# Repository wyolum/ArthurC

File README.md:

ArthurC
=======

rev 2 of i2GPS - called ArthurC in honor of Arthur C Clarke, who coined the idea of GPS

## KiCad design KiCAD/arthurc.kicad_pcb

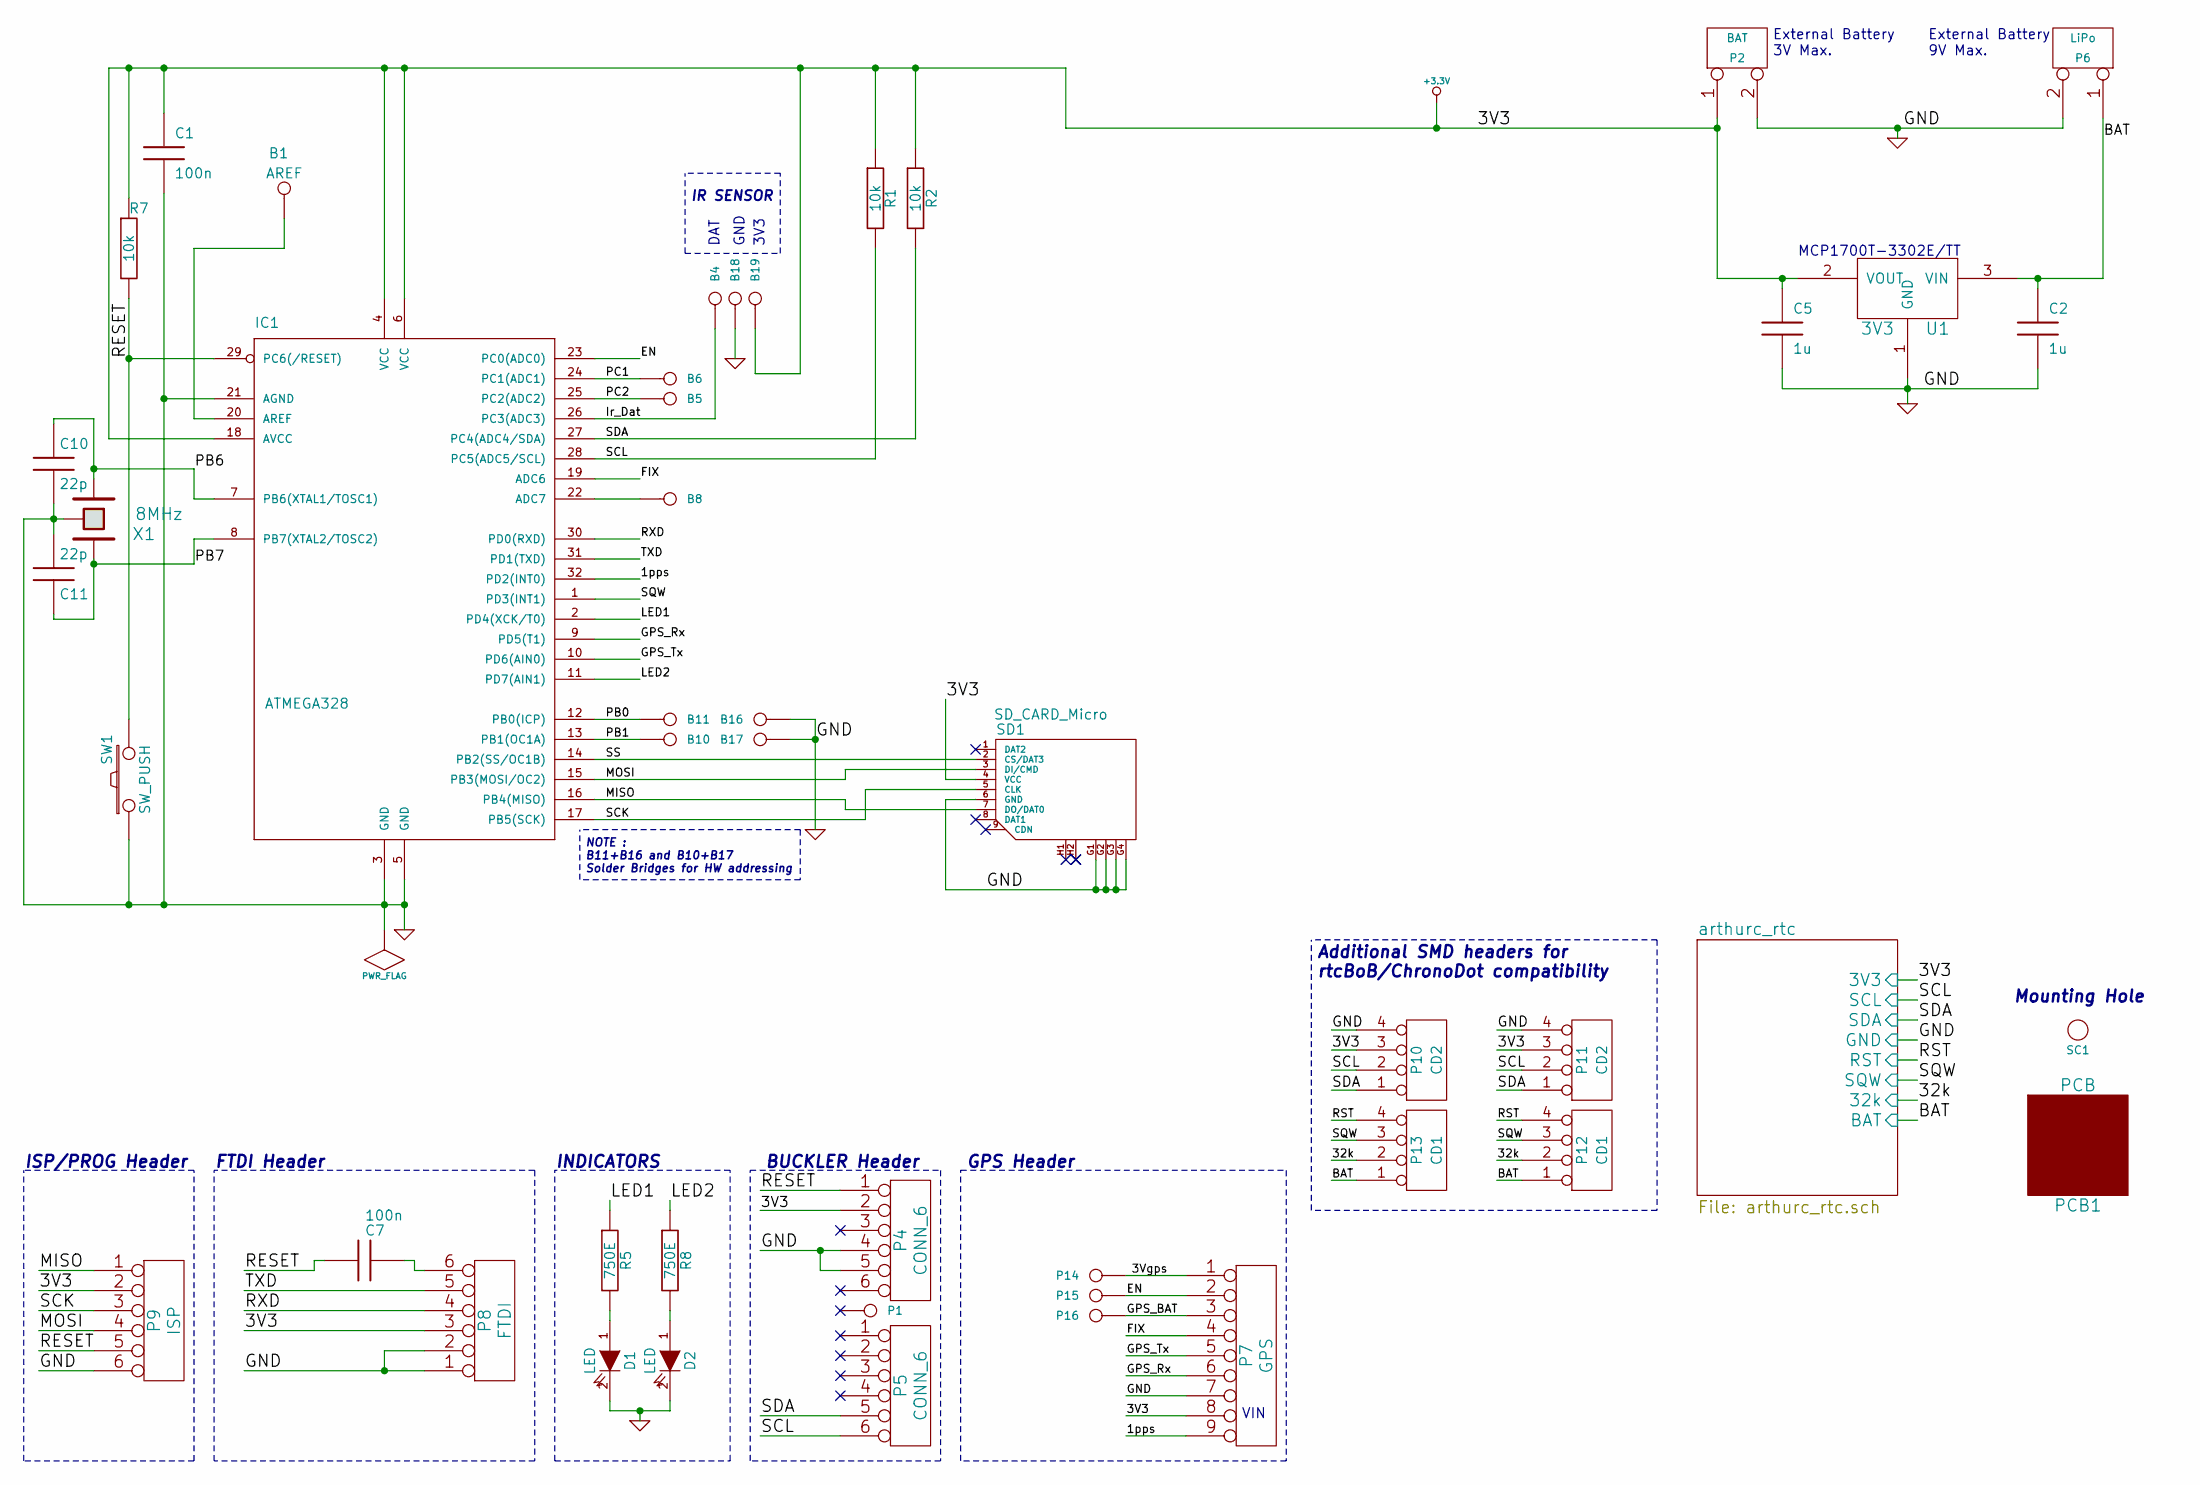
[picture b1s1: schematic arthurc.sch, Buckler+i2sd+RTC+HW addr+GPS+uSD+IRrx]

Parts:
B1: AREF
B4, B5, B6, B8, B18, B19: I/O; I%2fO
B10, B11, B16, B17: I/O; I%2fO_ADR
C1, C7: 100n; c_0805
C2, C5: 1u; c_0805
C10, C11: 22p; c_0805; Digikey 490-1734-1-ND
D1, D2: LED; d_0805
IC1: ATMEGA328; TQFP32
P1, P14, P15, P16: I/O; I%2fO
P2: BAT
P4, P5: CONN_6; PIN_ARRAY-6X1
P6: LiPo; pin_strip_2
P7: GPS; PIN_ARRAY-9X1
P8: FTDI; PIN_ARRAY-6X1
P9: ISP
P10, P11: CD2; Sck-04-F-SMT
P12, P13: CD1; Sck-04-F-SMT
PCB1: PCB
R1, R2, R7: 10k; r_0805
R5, R8: 750E; r_0805
SC1: SCREW; vite_3mm
SD1: SD_CARD_Micro
SW1: SW_PUSH; SW_SMD
U1: 3V3; SOT23-3; Part No MCP1700T-3302E/TT
X1: 8MHz; Xtal_SMD3

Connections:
+3.3V: B19.1, C1.1, C5.1, IC1.4 (VCC), IC1.6 (VCC), IC1.18 (AVCC), P2.1, P4.2, P7.8, P8.3, P9.2, P10.3, P11.3, R1.1, R2.1, R7.1, SD1.4 (VCC), U1.2 (VOUT); also elsewhere on the board
/1pps: IC1.32 (PD2(INT0)), P7.9
/3Vgps: P7.1, P14.1
/EN: IC1.23 (PC0(ADC0)), P7.2, P15.1
/FIX: IC1.19 (ADC6), P7.4
/GPS_BAT: P7.3, P16.1
/GPS_Rx: IC1.9 (PD5(T1)), P7.6
/GPS_Tx: IC1.10 (PD6(AIN0)), P7.5
/Ir_Dat: B4.1, IC1.26 (PC3(ADC3))
/LED1: IC1.2 (PD4(XCK/T0)), R5.1
/LED2: IC1.11 (PD7(AIN1)), R8.1
/MISO: IC1.16 (PB4(MISO)), P9.1, SD1.7 (DO/DAT0)
/MOSI: IC1.15 (PB3(MOSI/OC2)), P9.4, SD1.3 (DI/CMD)
/PB0: B11.1, IC1.12 (PB0(ICP))
/PB1: B10.1, IC1.13 (PB1(OC1A))
/PB6: C10.1, IC1.7 (PB6(XTAL1/TOSC1)), X1.1
/PB7: C11.2, IC1.8 (PB7(XTAL2/TOSC2)), X1.2
/PC1: B6.1, IC1.24 (PC1(ADC1))
/PC2: B5.1, IC1.25 (PC2(ADC2))
/RESET: C7.2, IC1.29 (PC6(/RESET)), P4.1, P9.5, R7.2, SW1.2
/RXD: IC1.30 (PD0(RXD)), P8.4
/SCK: IC1.17 (PB5(SCK)), P9.3, SD1.5 (CLK)
/SS: IC1.14 (PB2(SS/OC1B)), SD1.2 (CS/DAT3)
/TXD: IC1.31 (PD1(TXD)), P8.5
/arthurc_rtc/32k: P12.2, P13.2; also elsewhere on the board
/arthurc_rtc/BAT: C2.1, P6.1, P12.1, P13.1, U1.3 (VIN); also elsewhere on the board
/arthurc_rtc/RST: P12.4, P13.4; also elsewhere on the board
/arthurc_rtc/SCL: IC1.28 (PC5(ADC5/SCL)), P5.6, P10.2, P11.2, R1.2; also elsewhere on the board
/arthurc_rtc/SDA: IC1.27 (PC4(ADC4/SDA)), P5.5, P10.1, P11.1, R2.2; also elsewhere on the board
/arthurc_rtc/SQW: IC1.1 (PD3(INT1)), P12.3, P13.3; also elsewhere on the board
GND: B16.1, B17.1, B18.1, C1.2, C2.2, C5.2, C10.2, C11.1, D1.2 (K), D2.2 (K), IC1.3 (GND), IC1.5 (GND), IC1.21 (AGND), P2.2 (PM), P4.4, P4.5, P6.2 (PM), P7.7, P8.1, P8.2, P9.6, P10.4, P11.4, SD1.6 (GND), SD1.G1, SD1.G2, SD1.G3, SD1.G4, SW1.1, U1.1 (GND), X1.3; also elsewhere on the board
unnamed: B1.1, IC1.20 (AREF)
unnamed: B8.1, IC1.22 (ADC7)
unnamed: C7.1, P8.6
unnamed: D1.1 (A), R5.2
unnamed: D2.1 (A), R8.2

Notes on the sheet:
MCP1700T-3302E/TT
GPS Header
3V3
GND
DAT
IR SENSOR
NOTE : B11+B16 and B10+B17 Solder Bridges for HW addressing
External Battery 9V Max.
INDICATORS
FTDI Header
ISP/PROG Header
BUCKLER Header
Mounting Hole
Additional SMD headers for rtcBoB/ChronoDot compatibility
VIN
External Battery 3V Max.

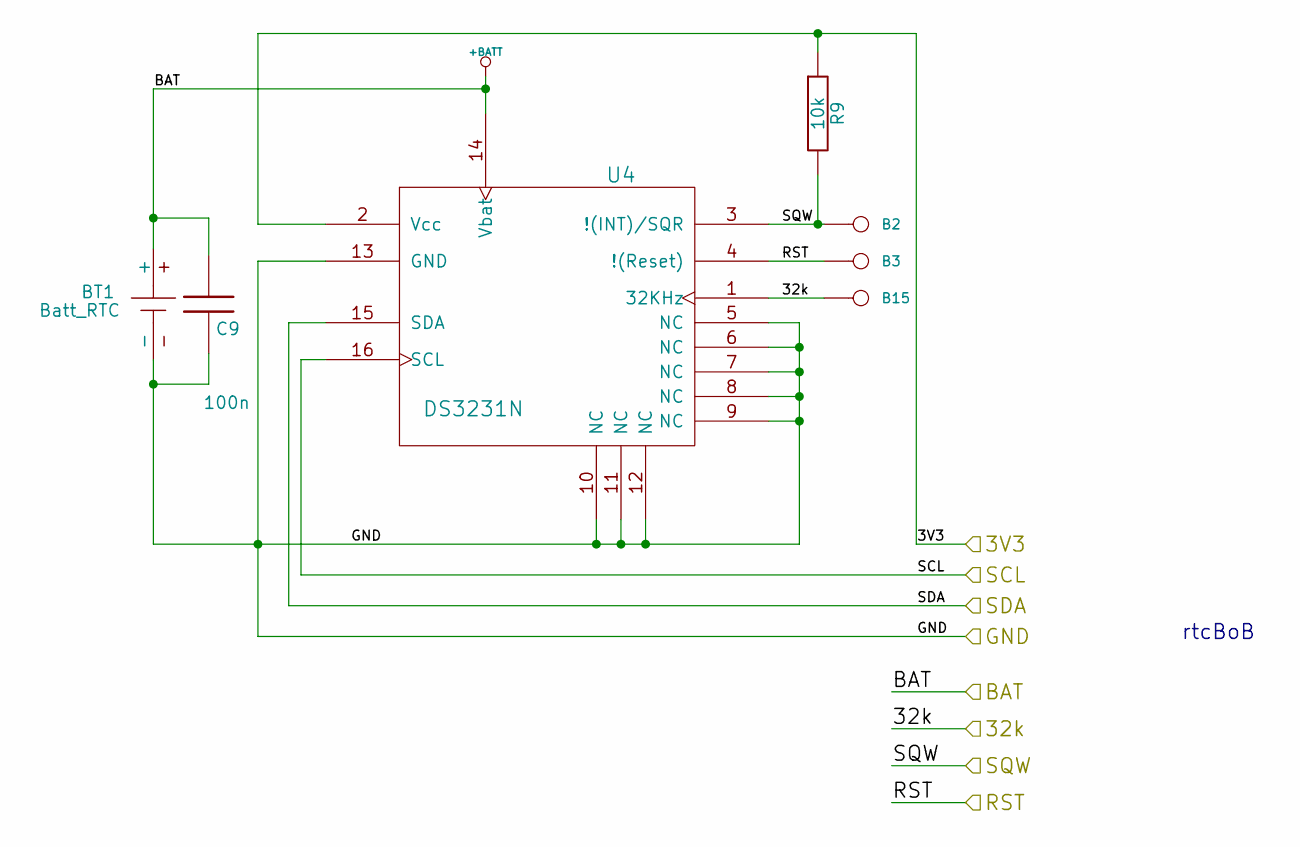
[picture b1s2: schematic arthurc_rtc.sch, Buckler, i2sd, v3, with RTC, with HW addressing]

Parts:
B2, B3, B15: I/O; I%2fO
BT1: Batt_RTC; Digikey BU2032SM-HD-GCT-ND
C9: 100n; c_0805
R9: 10k; r_0805
U4: DS3231N; DS3231

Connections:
+3.3V: R9.1, U4.2 (Vcc); also elsewhere on the board
/arthurc_rtc/32k: B15.1, U4.1 (32KHz); also elsewhere on the board
/arthurc_rtc/BAT: BT1.+, C9.1, U4.14 (Vbat); also elsewhere on the board
/arthurc_rtc/RST: B3.1, U4.4 (!(Reset)); also elsewhere on the board
/arthurc_rtc/SCL: U4.16 (SCL); also elsewhere on the board
/arthurc_rtc/SDA: U4.15 (SDA); also elsewhere on the board
/arthurc_rtc/SQW: B2.1, R9.2, U4.3 (!(INT)/SQR); also elsewhere on the board
GND: BT1.-, C9.2, U4.5 (NC), U4.6 (NC), U4.7 (NC), U4.8 (NC), U4.9 (NC), U4.10 (NC), U4.11 (NC), U4.12 (NC), U4.13 (GND); also elsewhere on the board

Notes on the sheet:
rtcBoB

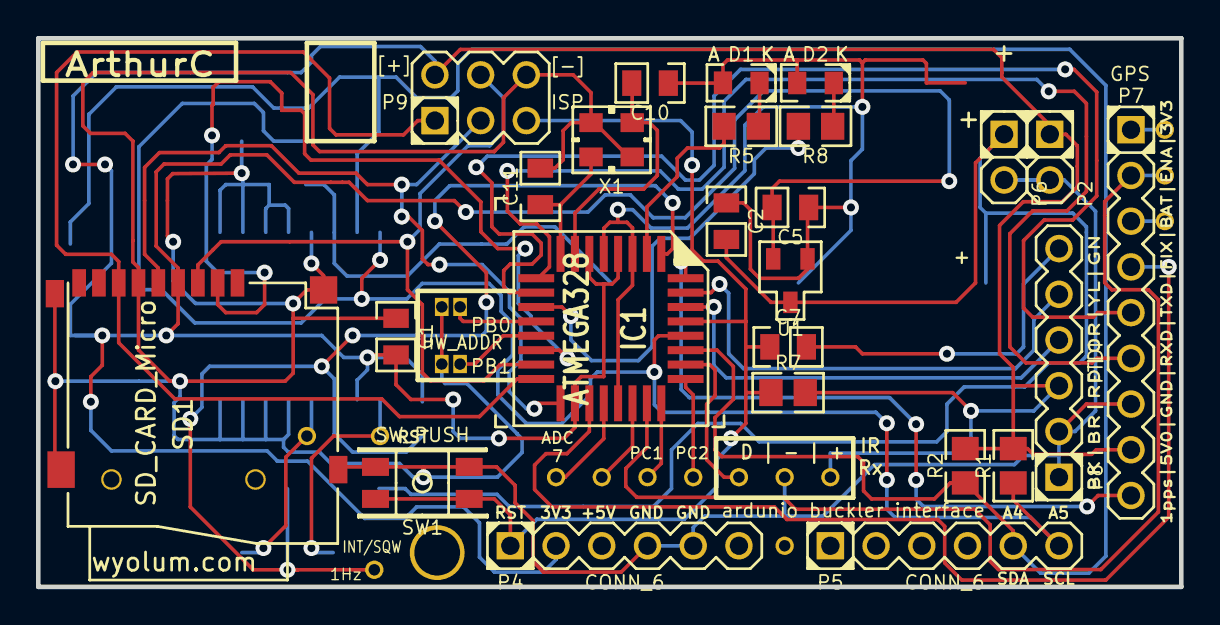
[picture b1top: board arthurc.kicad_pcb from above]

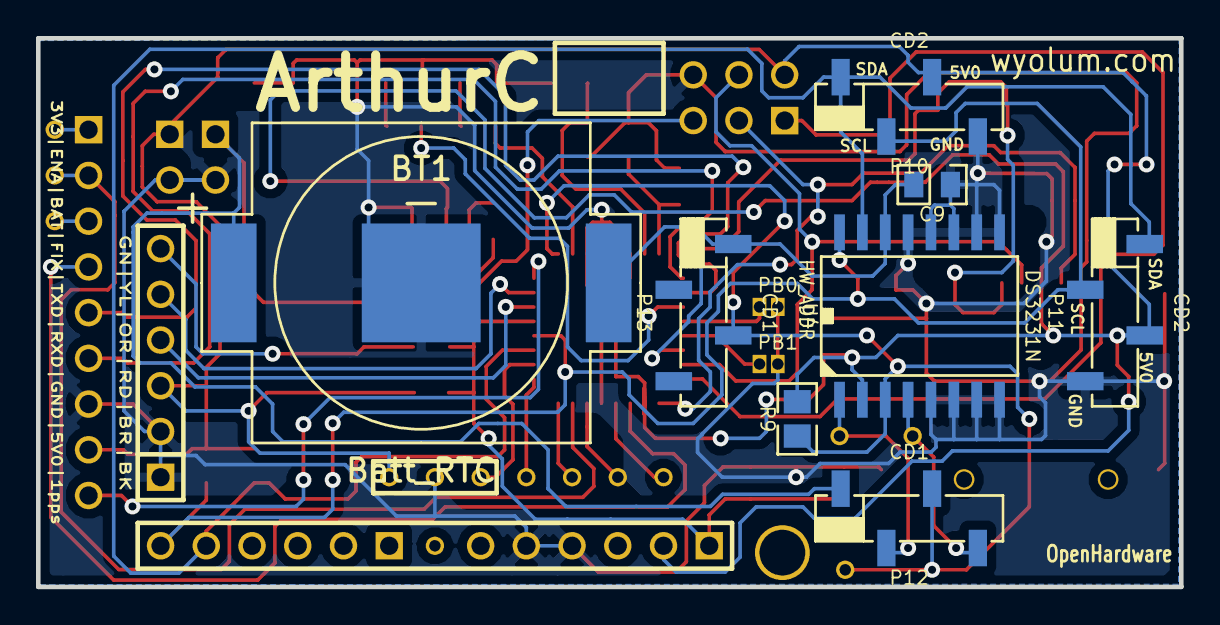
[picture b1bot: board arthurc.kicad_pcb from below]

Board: 2 copper layers, 63.5 x 30.5 mm, 53 parts (8 on the bottom side), 36 nets.

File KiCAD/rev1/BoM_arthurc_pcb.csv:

"Id";"Designator";"Package";"Quantity";"Designation";"Supplier and ref";
1;"B2,B3,B4,B5,B6,B8,B15,B18,B19,P1,P14,P15,P16";"ArthurC Lib:I%2fO";13;"I/O";;;
2;"B10,B11,B16,B17";"ArthurC Lib:I%2fO_ADR";4;"I/O";;;
3;"X1";"ArthurC Lib:Xtal_SMD3";1;"8MHz";;;
4;"P7";"ArthurC Lib:PIN_ARRAY-9X1";1;"GPS";;;
5;"B1";"ArthurC Lib:I%2fO";1;"AREF";;;
6;"P2";"ArthurC Lib:pin_strip_2";1;"BAT";;;
7;"BT1";"ArthurC Lib:CR1632";1;"Batt_RTC";;;
8;"C1,C7,C9";"ArthurC Lib:c_0805";3;"100n";;;
9;"C2,C5";"ArthurC Lib:c_0805";2;"1u";;;
10;"C10,C11";"ArthurC Lib:c_0805";2;"22p";;;
11;"D1,D2";"ArthurC Lib:d_0805";2;"LED";;;
12;"IC1";"ArthurC Lib:TQFP32";1;"ATMEGA328";;;
13;"P4,P5";"ArthurC Lib:PIN_ARRAY-6X1";2;"CONN_6";;;
14;"P6";"ArthurC Lib:pin_strip_2";1;"LiPo";;;
15;"P8";"ArthurC Lib:PIN_ARRAY-6X1";1;"FTDI";;;
16;"P9";"ArthurC Lib:ISP";1;"ISP";;;
17;"P10,P11";"ArthurC Lib:Sck-04-F-SMT";2;"CD2";;;
18;"P12,P13";"ArthurC Lib:Sck-04-F-SMT";2;"CD1";;;
19;"PCB1";"ArthurC Lib:PCB";1;"PCB";;;
20;"R1,R2,R7,R9";"ArthurC Lib:r_0805";4;"10k";;;
21;"R5,R8";"ArthurC Lib:r_0805";2;"750E";;;
22;"SC1";"ArthurC Lib:vite_3mm";1;"SCREW";;;
23;"SD1";"ArthurC Lib:SD_Micro";1;"SD_CARD_Micro";;;
24;"SW1";"ArthurC Lib:SW_SMD";1;"SW_PUSH";;;
25;"U1";"ArthurC Lib:SOT23-3";1;"3V3";;;
26;"U4";"ArthurC Lib:DS3231";1;"DS3231N";;;
27;"C3";"ArthurC Lib:C_ELCO_SMD";1;"47uF_25V";;;

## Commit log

2014-03-01 first commit of ArthurC - which is rev2 of i2GPS
2014-03-01 re-organized to wyolum standard directory structure, added gps datasheet
2014-03-06 ArthurC work in progress
2014-04-01 Ultimate GPS header added to I2GPS
2014-04-02 work in progress
2014-04-27 work in progress, converting design to work on 3V3
2014-04-29 schematic needs final review before starting board layout
2014-05-07 board layout work in progress
2014-05-20 ArthurC rev1 work in progress. Added rev2 directory for USB version
2014-05-22 ArthurC rev1 (FTDI ver) complete.
2014-05-24 ArthurC rev1 ready. Added LED breakout pads
2014-05-25 ArthurC rev2 work in progress
2014-05-27 breakout pads made bigger in ArthurC_rev1
2014-05-28 final ArthurC rev1
2014-06-26 just syncing my folders, nothing new here
2014-09-26 added seeed SD Card datasheet
